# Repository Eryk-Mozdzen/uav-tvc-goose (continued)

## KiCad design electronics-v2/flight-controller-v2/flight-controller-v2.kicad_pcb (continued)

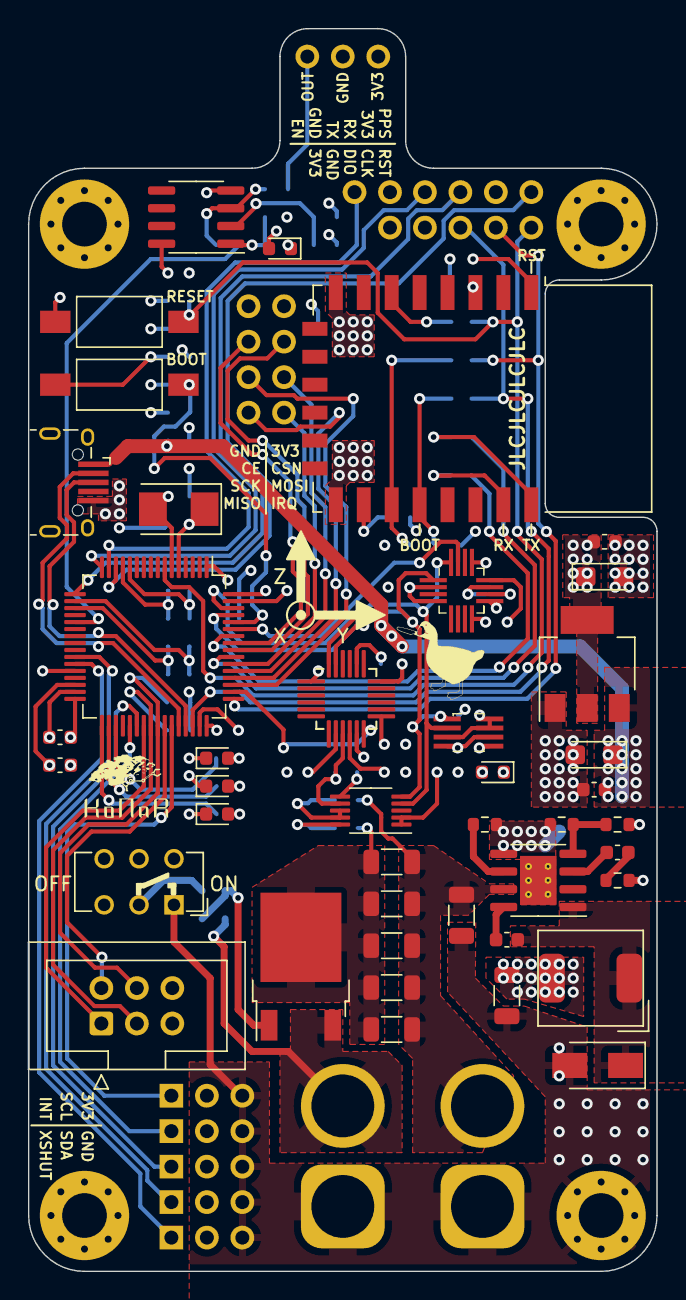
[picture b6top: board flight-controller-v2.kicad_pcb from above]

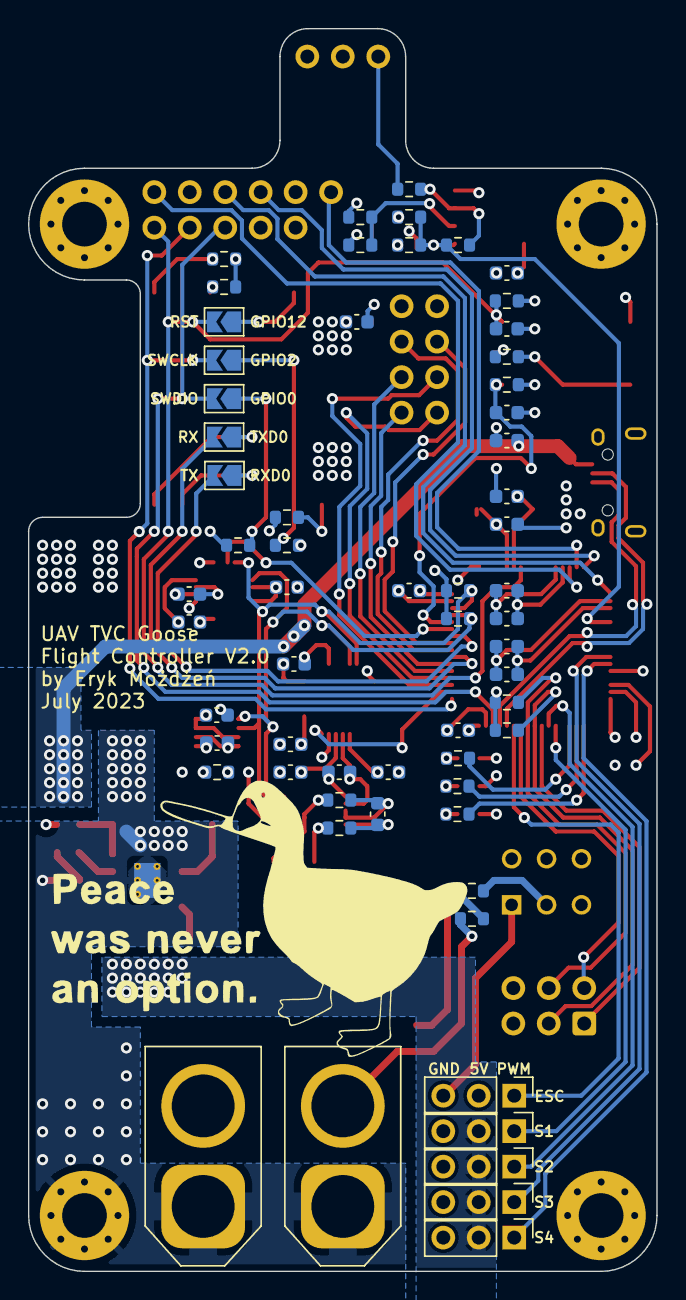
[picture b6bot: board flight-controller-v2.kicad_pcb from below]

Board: 4 copper layers, 45.0 x 89.0 mm, 112 parts (62 on the bottom side), 76 nets.

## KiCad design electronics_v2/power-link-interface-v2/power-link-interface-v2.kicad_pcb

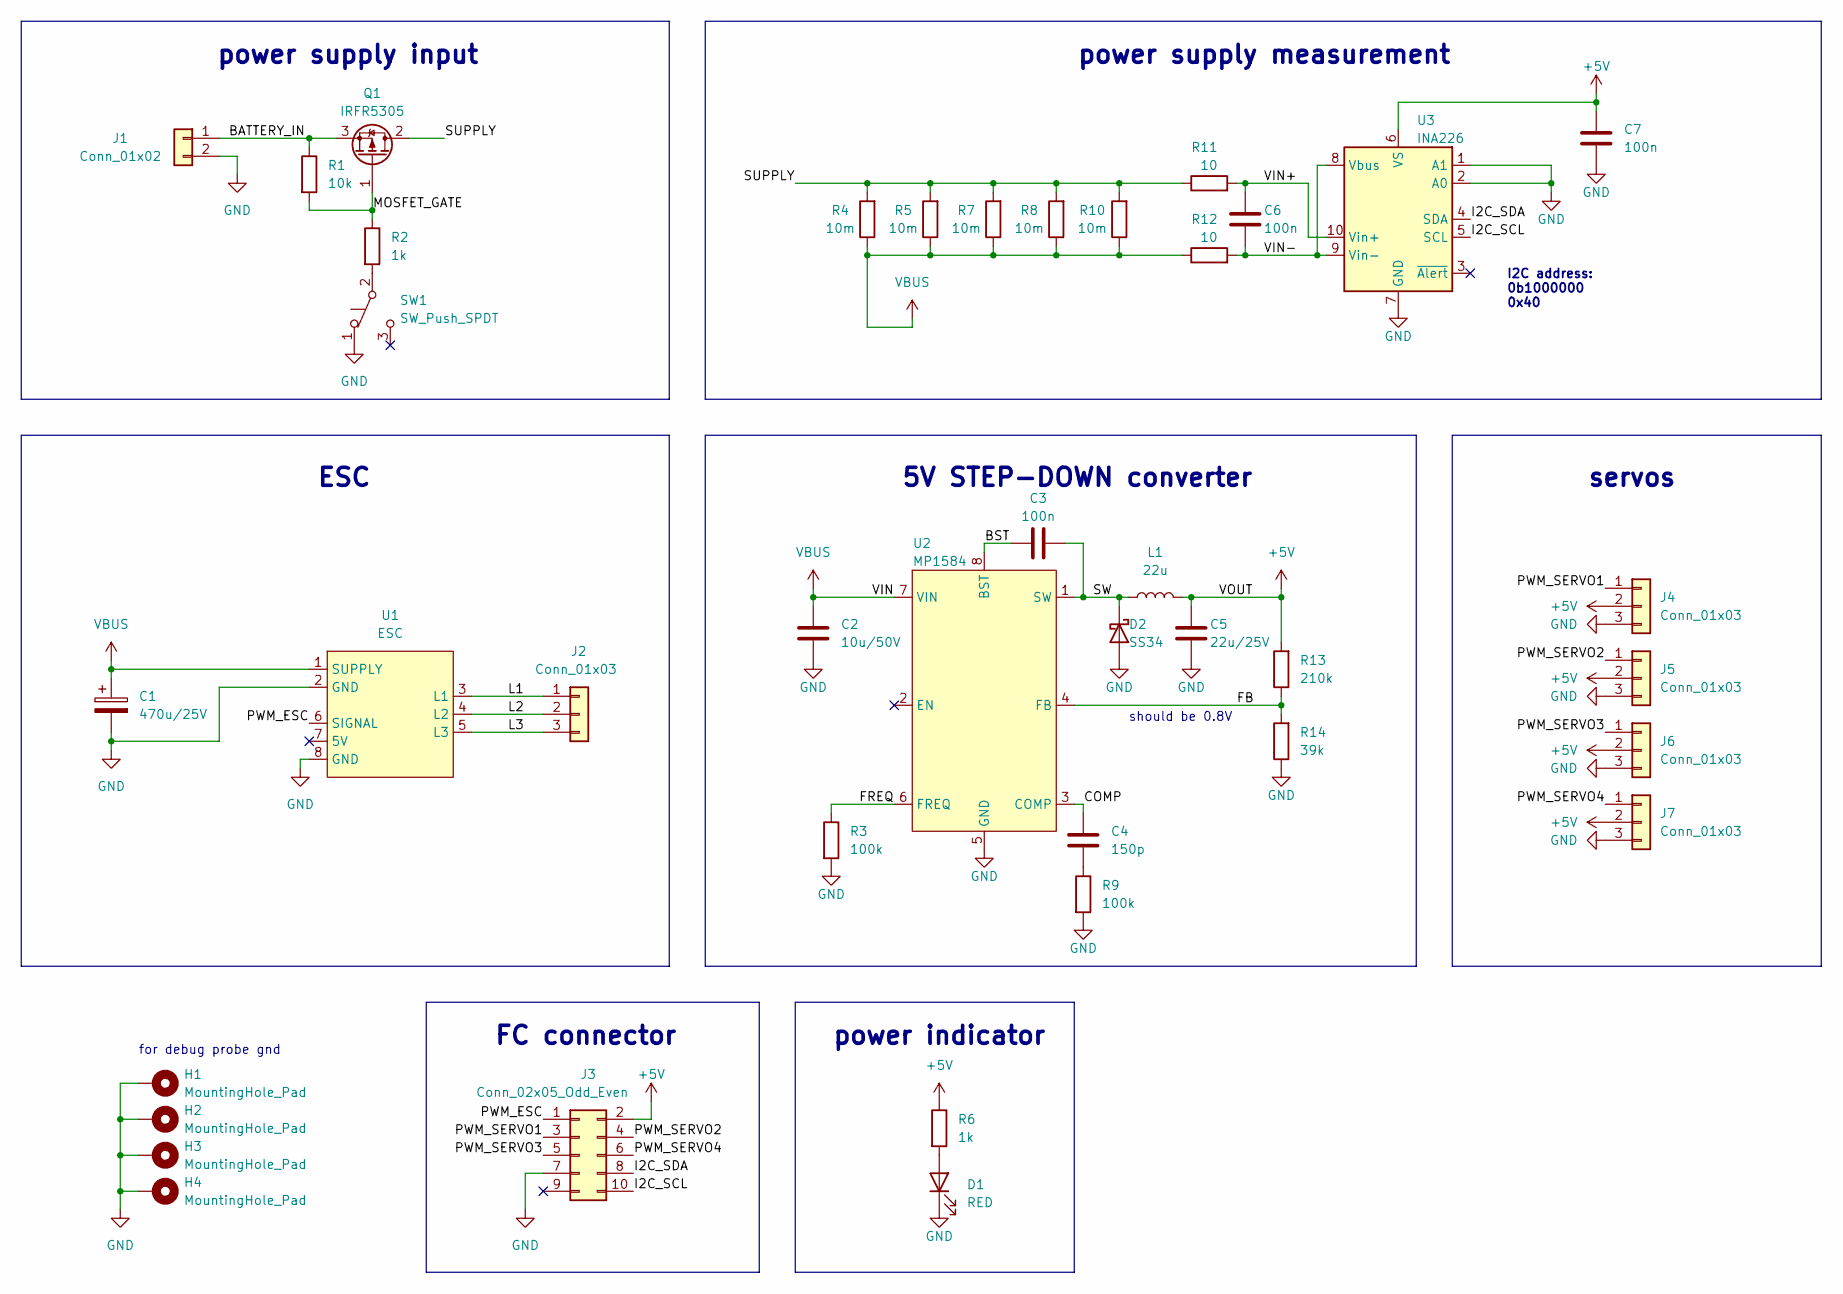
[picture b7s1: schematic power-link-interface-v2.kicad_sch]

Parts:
C1: 470u/25V; C_Radial_D8.0mm_H11.5mm_P3.50mm
C2: 10u/50V; C_1206_3216Metric
C3, C6, C7: 100n; C_0603_1608Metric
C4: 150p; C_0603_1608Metric
C5: 22u/25V; C_1206_3216Metric
D1: RED; LED_0603_1608Metric
D2: SS34; D_SMA
H1, H2, H3, H4: MountingHole_Pad; MountingHole_3.2mm_M3_Pad_Via
J1: Conn_01x02; AMASS_XT60PW-M
J2: Conn_01x03; tht_pin_01x03
J3: Conn_02x05_Odd_Even; IDC-Header_2x05_P2.54mm_Vertical
J4, J5, J6, J7: Conn_01x03; PinHeader_1x03_P2.54mm_Vertical
L1: 22u; L_AVX_LMLP07A7
Q1: IRFR5305; TO-252-2
R1: 10k; R_0603_1608Metric
R2, R6: 1k; R_0603_1608Metric
R3, R9: 100k; R_0603_1608Metric
R4, R5, R7, R8, R10: 10m; R_1206_3216Metric
R11, R12: 10; R_0603_1608Metric
R13: 210k; R_0603_1608Metric
R14: 39k; R_0603_1608Metric
SW1: SW_Push_SPDT; SW_CuK_JS202011CQN_DPDT_Straight
U1: ESC
U2: MP1584; SOIC-8-1EP_3.9x4.9mm_P1.27mm_EP2.62x3.51mm_ThermalVias
U3: INA226; VSSOP-10_3x3mm_P0.5mm

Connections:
+5V: C5.2, C7.2, J3.2, J4.2, J5.2, J6.2, J7.2, L1.2, R6.1, R13.2, U3.6 (VS)
/BATTERY_IN: J1.1, Q1.3 (S), R1.1
/BST: C3.1, U2.8 (BST)
/COMP: C4.1, U2.3 (COMP)
/FB: R13.1, R14.2, U2.4 (FB)
/FREQ: R3.1, U2.6 (FREQ)
/I2C_SCL: J3.10, U3.5 (SCL)
/I2C_SDA: J3.8, U3.4 (SDA)
/L1: J2.1, U1.3 (L1)
/L2: J2.2, U1.4 (L2)
/L3: J2.3, U1.5 (L3)
/MOSFET_GATE: Q1.1 (G), R1.2, R2.1
/PWM_ESC: J3.1, U1.6 (SIGNAL)
/PWM_SERVO1: J3.3, J4.1
/PWM_SERVO2: J3.4, J5.1
/PWM_SERVO3: J3.5, J6.1
/PWM_SERVO4: J3.6, J7.1
/SUPPLY: Q1.2 (D), R4.2, R5.2, R7.2, R8.2, R10.2, R11.1
/SW: C3.2, D2.1 (K), L1.1, U2.1 (SW)
/VIN+: C6.2, R11.2, U3.10 (Vin+)
/VIN-: C6.1, R12.2, U3.8 (Vbus), U3.9 (Vin-)
GND: C1.2, C2.1, C5.1, C7.1, D1.1 (K), D2.2 (A), H1.1, H2.1, H3.1, H4.1, J1.2, J3.7, J4.3, J5.3, J6.3, J7.3, R3.2, R9.2, R14.1, SW1.1 (A), U1.2 (GND), U1.8 (GND), U2.5 (GND), U3.1 (A1), U3.2 (A0), U3.7 (GND)
unnamed: C4.2, R9.1
unnamed: D1.2 (A), R6.2
unnamed: R2.2, SW1.2 (B)
VBUS: C1.1, C2.2, R4.1, R5.1, R7.1, R8.1, R10.1, R12.1, U1.1 (SUPPLY), U2.7 (VIN)

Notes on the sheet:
I2C address: 0b1000000 0x40
FC connector
power supply input
power supply measurement
ESC
for debug probe gnd
power indicator
5V STEP-DOWN converter
servos
should be 0.8V

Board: 2 copper layers, 40 parts (0 on the bottom side), 26 nets, no tracks yet.

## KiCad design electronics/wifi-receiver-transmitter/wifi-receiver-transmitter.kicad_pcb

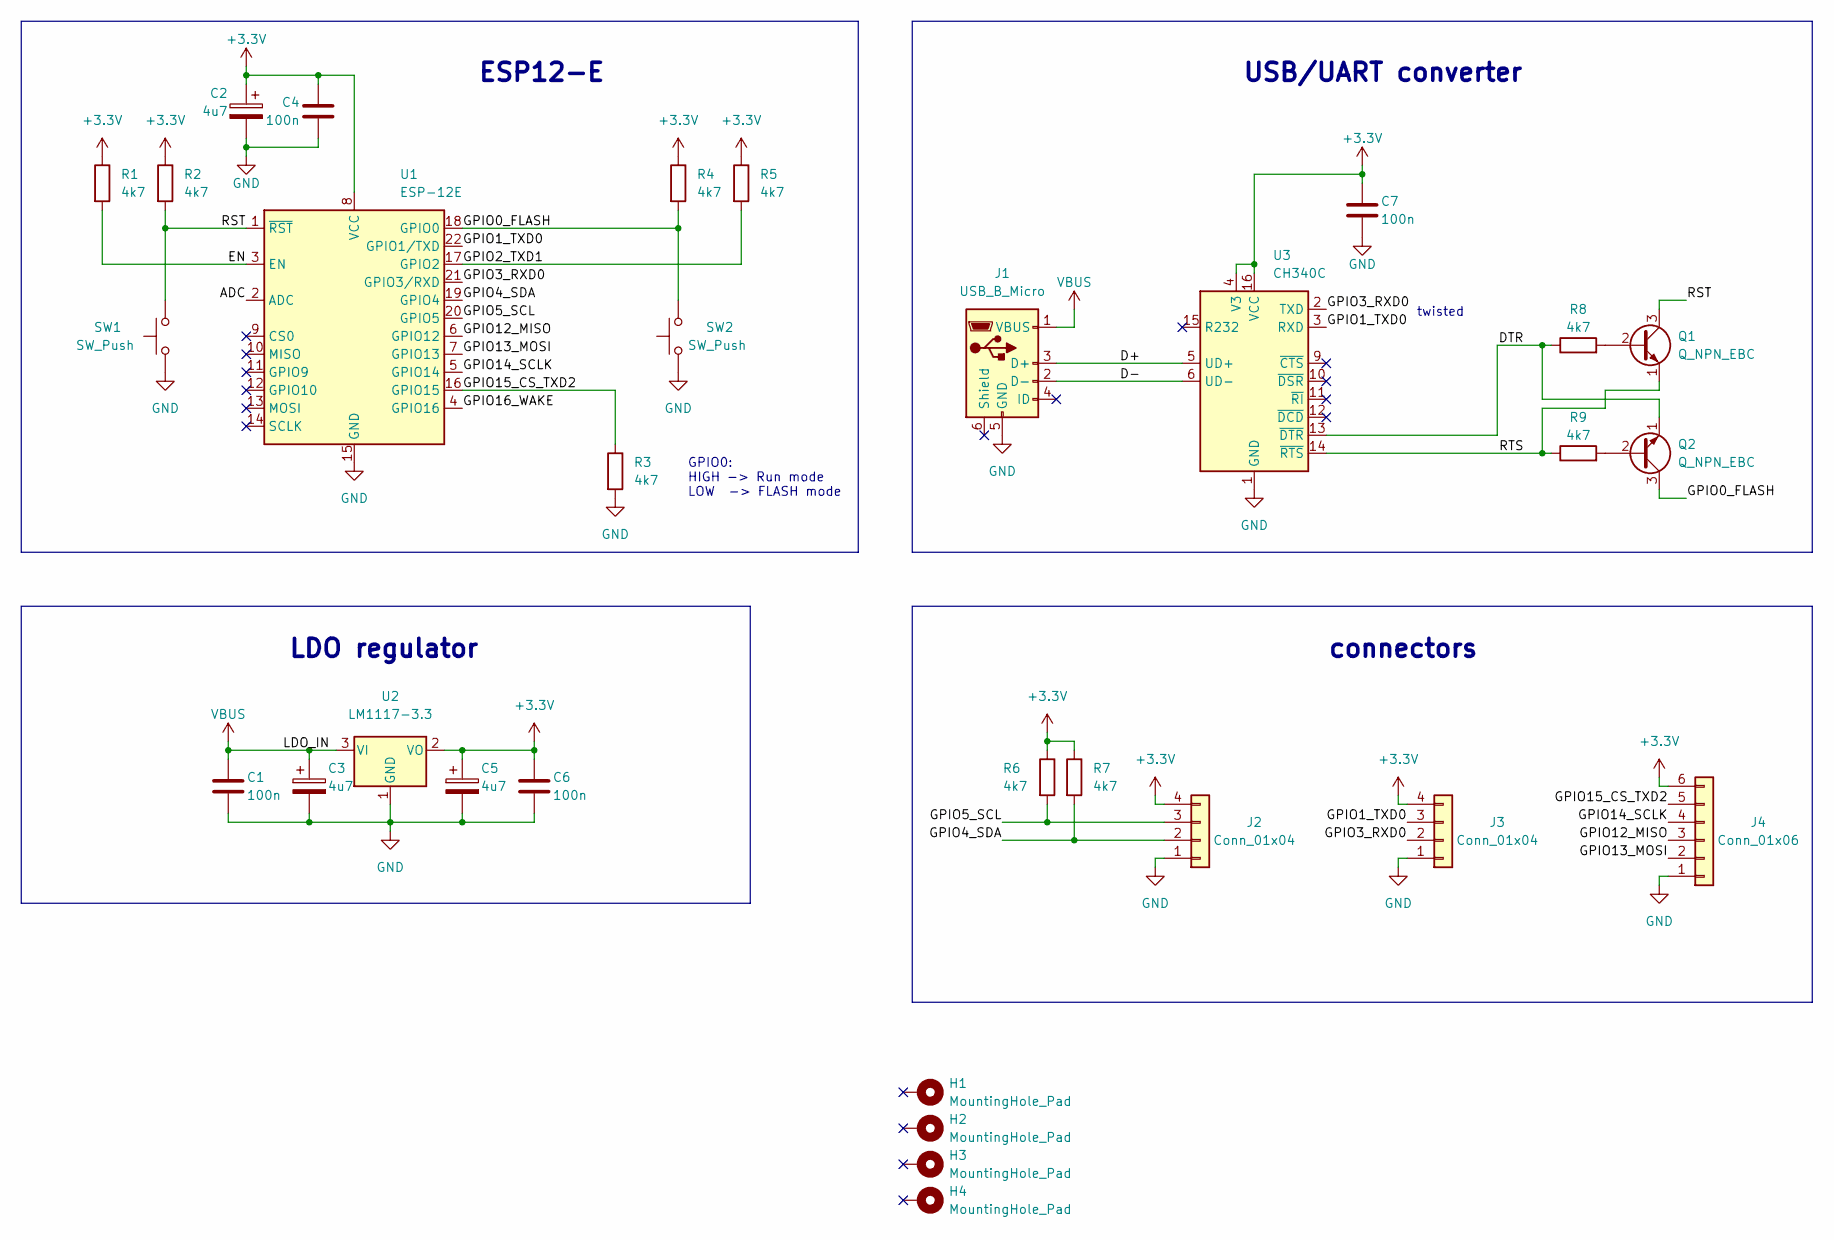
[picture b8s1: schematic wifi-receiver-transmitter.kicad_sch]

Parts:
C1, C4, C6, C7: 100n; C_0603_1608Metric
C2, C3, C5: 4u7; CP_EIA-3216-18_Kemet-A
H1, H2, H3, H4: MountingHole_Pad; MountingHole_3.2mm_M3_Pad_Via
J1: USB_B_Micro; usb_micro_B_druk_II
J2, J3: Conn_01x04; tht_pin_01x04
J4: Conn_01x06; tht_pin_01x06
Q1, Q2: Q_NPN_EBC; SOT-23
R1, R2, R3, R4, R5, R6, R7, R8, R9: 4k7; R_0603_1608Metric
SW1, SW2: SW_Push; SW_Push_SPST_NO_Alps_SKRK
U1: ESP-12E
U2: LM1117-3.3; SOT-223-3_TabPin2
U3: CH340C; SOIC-16_3.9x9.9mm_P1.27mm

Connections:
+3.3V: C2.1, C4.1, C5.1, C6.1, C7.1, J2.4, J3.4, J4.6, R1.1, R2.1, R4.1, R5.1, R6.1, R7.1, U1.8 (VCC), U2.2 (VO), U3.4 (V3), U3.16 (VCC)
/ADC: U1.2 (ADC)
/D+: J1.3 (D+), U3.5 (UD+)
/D-: J1.2 (D-), U3.6 (UD-)
/DTR: Q2.1 (E), R8.1, U3.13 (~DTR)
/EN: R1.2, U1.3 (EN)
/GPIO0_FLASH: Q2.3 (C), R4.2, SW2.2, U1.18 (GPIO0)
/GPIO1_TXD0: J3.3, U1.22 (GPIO1/TXD), U3.3 (RXD)
/GPIO2_TXD1: R5.2, U1.17 (GPIO2)
/GPIO3_RXD0: J3.2, U1.21 (GPIO3/RXD), U3.2 (TXD)
/GPIO4_SDA: J2.2, R7.2, U1.19 (GPIO4)
/GPIO5_SCL: J2.3, R6.2, U1.20 (GPIO5)
/GPIO12_MISO: J4.3, U1.6 (GPIO12)
/GPIO13_MOSI: J4.2, U1.7 (GPIO13)
/GPIO14_SCLK: J4.4, U1.5 (GPIO14)
/GPIO15_CS_TXD2: J4.5, R3.1, U1.16 (GPIO15)
/GPIO16_WAKE: U1.4 (GPIO16)
/RST: Q1.3 (C), R2.2, SW1.2, U1.1 (~RST)
/RTS: Q1.1 (E), R9.1, U3.14 (~RTS)
GND: C1.2, C2.2, C3.2, C4.2, C5.2, C6.2, C7.2, J1.5 (GND), J2.1, J3.1, J4.1, R3.2, SW1.1, SW2.1, U1.15 (GND), U2.1 (GND), U3.1 (GND)
unnamed: Q1.2 (B), R8.2
unnamed: Q2.2 (B), R9.2
VBUS: C1.1, C3.1, J1.1 (VBUS), U2.3 (VI)

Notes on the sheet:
ESP12-E
USB/UART converter
GPIO0: HIGH -> Run mode LOW -> FLASH mode
LDO regulator
twisted
connectors

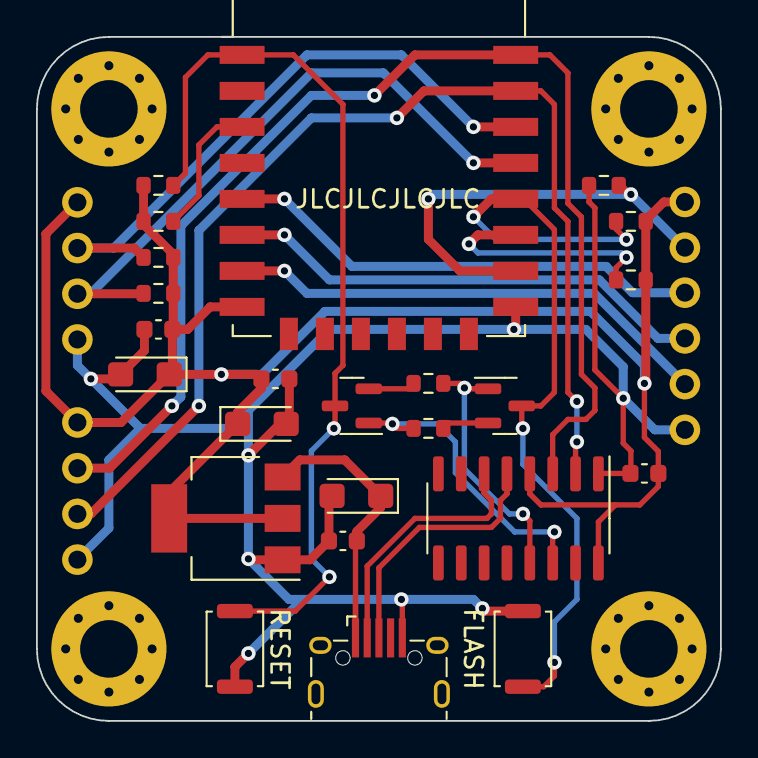
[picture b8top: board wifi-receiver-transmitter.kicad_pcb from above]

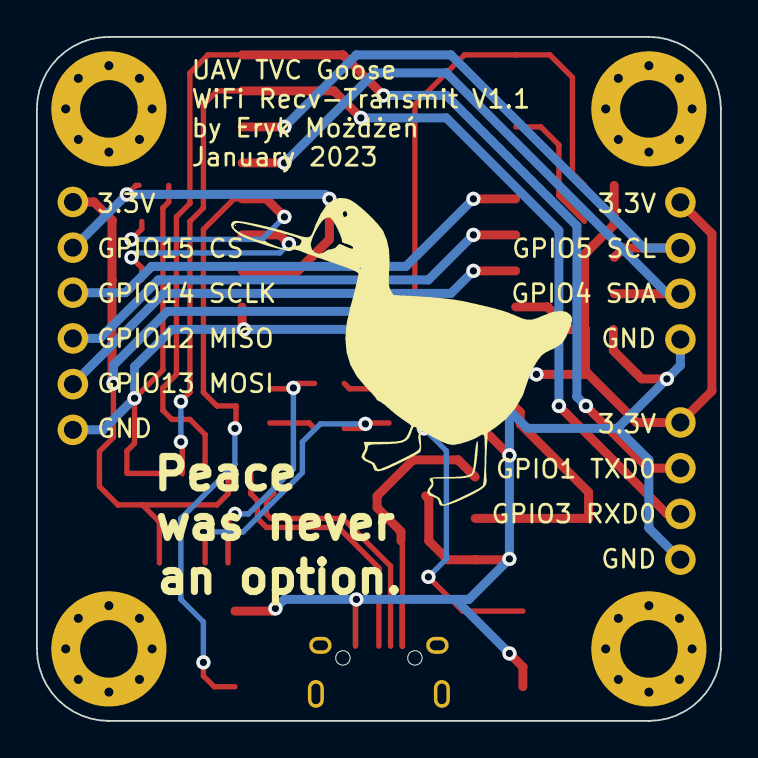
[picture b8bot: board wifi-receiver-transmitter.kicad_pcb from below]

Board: 2 copper layers, 38.0 x 38.0 mm, 31 parts (2 on the bottom side), 21 nets.

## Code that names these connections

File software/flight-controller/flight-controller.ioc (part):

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Mcu.Name=STM32U535RETx
Mcu.Package=LQFP64
Mcu.UserName=STM32U535RETx
PA0.GPIOParameters=GPIO_Label
PA0.GPIO_Label=TACHO
PA0.Signal=S_TIM2_ETR
PA10.GPIOParameters=GPIO_Label
PA10.GPIO_Label=SERVO1
PA10.Signal=S_TIM1_CH3
PA11.GPIOParameters=GPIO_Label
PA11.GPIO_Label=ESC
PA11.Signal=S_TIM1_CH4
PA13\ (JTMS/SWDIO).Mode=Serial_Wire
PA13\ (JTMS/SWDIO).Signal=DEBUG_JTMS-SWDIO
PA14\ (JTCK/SWCLK).Mode=Serial_Wire
PA14\ (JTCK/SWCLK).Signal=DEBUG_JTCK-SWCLK
PA4.GPIOParameters=GPIO_Label
PA4.GPIO_Label=FLOW_CS
PA4.Signal=GPIO_Output
PA5.GPIOParameters=GPIO_Label
PA5.GPIO_Label=FLOW_SCK
PA5.Mode=Full_Duplex_Master
PA5.Signal=SPI1_SCK
PA6.GPIOParameters=GPIO_Label
PA6.GPIO_Label=FLOW_MISO
PA6.Mode=Full_Duplex_Master
PA6.Signal=SPI1_MISO
PA7.GPIOParameters=GPIO_Label
PA7.GPIO_Label=FLOW_MOSI
PA7.Mode=Full_Duplex_Master
PA7.Signal=SPI1_MOSI
PA8.GPIOParameters=GPIO_Label
PA8.GPIO_Label=SERVO3
PA8.Signal=S_TIM1_CH1
PA9.GPIOParameters=GPIO_Label
PA9.GPIO_Label=SERVO2
PA9.Signal=S_TIM1_CH2
PB1.GPIOParameters=GPIO_Label
PB1.GPIO_Label=LED_G
PB1.Signal=GPIO_Output
PB12.GPIOParameters=GPIO_Label
PB12.GPIO_Label=LED_R
PB12.Signal=GPIO_Output
PB15.GPIOParameters=GPIO_Label,GPIO_ModeDefaultEXTI
PB15.GPIO_Label=RANGE_ECHO
PB15.GPIO_ModeDefaultEXTI=GPIO_MODE_IT_RISING_FALLING
PB15.Signal=GPXTI15
PB2.GPIOParameters=GPIO_Label
PB2.GPIO_Label=LED_B
PB2.Signal=GPIO_Output
PB3\ (JTDO/TRACESWO).GPIOParameters=GPIO_Label
PB3\ (JTDO/TRACESWO).GPIO_Label=IMU_INT
PB3\ (JTDO/TRACESWO).Signal=GPXTI3
PB5.GPIOParameters=GPIO_Label,GPIO_ModeDefaultEXTI
PB5.GPIO_Label=PWR_INT
PB5.GPIO_ModeDefaultEXTI=GPIO_MODE_IT_FALLING
PB5.Signal=GPXTI5
PB6.GPIOParameters=GPIO_Speed,GPIO_Label
PB6.GPIO_Label=MISC_SCL
PB6.GPIO_Speed=GPIO_SPEED_FREQ_VERY_HIGH
PB6.Mode=I2C
PB6.Signal=I2C4_SCL
PB7.GPIOParameters=GPIO_Speed,GPIO_Label
PB7.GPIO_Label=MISC_SDA
PB7.GPIO_Speed=GPIO_SPEED_FREQ_VERY_HIGH
PB7.Mode=I2C
PB7.Signal=I2C4_SDA
PB8.GPIOParameters=GPIO_Speed,GPIO_Label
PB8.GPIO_Label=IMU_SCL
PB8.GPIO_Speed=GPIO_SPEED_FREQ_VERY_HIGH
PB8.Mode=I2C
PB8.Signal=I2C1_SCL
PB9.GPIOParameters=GPIO_Speed,GPIO_Label
PB9.GPIO_Label=IMU_SDA
PB9.GPIO_Speed=GPIO_SPEED_FREQ_VERY_HIGH
PB9.Mode=I2C
PB9.Signal=I2C1_SDA
PC0.GPIOParameters=GPIO_Speed,GPIO_Label
PC0.GPIO_Label=MAG_SCL
PC0.GPIO_Speed=GPIO_SPEED_FREQ_VERY_HIGH
PC0.Mode=I2C
PC0.Signal=I2C3_SCL
PC1.GPIOParameters=GPIO_Speed,GPIO_Label
PC1.GPIO_Label=MAG_SDA
PC1.GPIO_Speed=GPIO_SPEED_FREQ_VERY_HIGH
PC1.Mode=I2C
PC1.Signal=I2C3_SDA
PC10.GPIOParameters=GPIO_Label
PC10.GPIO_Label=ESP_RXD
PC10.Mode=Asynchronous
PC10.Signal=UART4_TX
PC11.GPIOParameters=GPIO_Label
PC11.GPIO_Label=ESP_TXD
PC11.Mode=Asynchronous
PC11.Signal=UART4_RX
PC12.GPIOParameters=GPIO_Label
PC12.GPIO_Label=GPS_RXD
PC12.Mode=Asynchronous
PC12.Signal=UART5_TX
PC13.GPIOParameters=GPIO_Label
PC13.GPIO_Label=LOAD_RATE
PC13.Signal=GPIO_Output
PC14-OSC32_IN\ (PC14).GPIOParameters=GPIO_Label
PC14-OSC32_IN\ (PC14).GPIO_Label=LOAD_DOUT
PC14-OSC32_IN\ (PC14).Signal=GPIO_Input
PC15-OSC32_OUT\ (PC15).GPIOParameters=GPIO_Label
PC15-OSC32_OUT\ (PC15).GPIO_Label=LOAD_SCK
PC15-OSC32_OUT\ (PC15).Signal=GPIO_Output
PC2.GPIOParameters=GPIO_Label
PC2.GPIO_Label=MAG_INT
PC2.Signal=GPXTI2
PC4.GPIOParameters=GPIO_Label,GPIO_ModeDefaultEXTI
PC4.GPIO_Label=FLOW_INT
PC4.GPIO_ModeDefaultEXTI=GPIO_MODE_IT_FALLING
PC4.Signal=GPXTI4
PC6.GPIOParameters=GPIO_Label
PC6.GPIO_Label=RANGE_TRIG
PC6.Signal=S_TIM8_CH1
PD2.GPIOParameters=GPIO_Label
PD2.GPIO_Label=GPS_TXD
PD2.Mode=Asynchronous
PD2.Signal=UART5_RX
PH0-OSC_IN\ (PH0).Mode=HSE-External-Oscillator
PH0-OSC_IN\ (PH0).Signal=RCC_OSC_IN
PH1-OSC_OUT\ (PH1).Mode=HSE-External-Oscillator
PH1-OSC_OUT\ (PH1).Signal=RCC_OSC_OUT
RCC.HSE_VALUE=8000000
RCC.SYSCLKFreq_VALUE=160000000
RCC.SYSCLKSource=RCC_SYSCLKSOURCE_PLLCLK
board=custom

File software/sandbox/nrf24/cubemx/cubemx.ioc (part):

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Mcu.Name=STM32U083RCTx
Mcu.Package=LQFP64
Mcu.UserName=STM32U083RCTx
PA1.Mode=Full_Duplex_Master
PA1.Signal=SPI2_SCK
PA10.Signal=GPIO_Output
PA2.Mode=Asynchronous
PA2.Signal=USART2_TX
PA3.Mode=Asynchronous
PA3.Signal=USART2_RX
PA5.Signal=GPIO_Output
PA8.Signal=GPIO_Output
PB3.Mode=Full_Duplex_Master
PB3.Signal=SPI1_SCK
PB4.Mode=Full_Duplex_Master
PB4.Signal=SPI1_MISO
PB5.Mode=Full_Duplex_Master
PB5.Signal=SPI1_MOSI
PC0.Signal=GPIO_Output
PC1.Signal=GPIO_Output
PC13.GPIOParameters=GPIO_PuPd
PC13.GPIO_PuPd=GPIO_PULLUP
PC13.Signal=GPIO_Input
PC2.Mode=Full_Duplex_Master
PC2.Signal=SPI2_MISO
PC3.Mode=Full_Duplex_Master
PC3.Signal=SPI2_MOSI
RCC.HSE_VALUE=4000000
RCC.SYSCLKFreq_VALUE=56000000
RCC.SYSCLKSource=RCC_SYSCLKSOURCE_PLLCLK
board=custom

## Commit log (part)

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2023-04-16 better icons and colors
2023-04-16 battery and fill
2023-04-16 better scaling
2023-04-16 smooth colors
2023-04-16 add voltage and current
2023-04-16 add altimeter
2023-04-17 add constrain to level
2023-04-17 add prefix to battery level
2023-04-17 remove battery prefix
2023-04-18 moved units
2023-04-18 removed empty line
2023-04-18 add USB data queue
2023-04-18 reverse order of byts in usb work xd
2023-04-25 add first comments
2023-05-04 signle mesurement work
2023-05-05 VLX work on interrupt
2023-05-05 moce read to task
2023-05-05 add slave recovery, increase queues
2023-05-09 Added scene without measurements
2023-05-09 logger show real data
2023-05-09 add doxygen comments
2023-05-09 simpler cmake, recursion
2023-05-20 power stats task
2023-05-20 ADC over DMA and scaling
2023-05-20 move sensor telemetry from estimator to sensors
2023-05-20 add const interval also to power and pressure
2023-05-21 move attitude estimation to separate class
2023-05-21 start of altitude and battery estimators
2023-05-21 increase timer queue length
2023-05-21 add high water mark for stack and decrease stacks
2023-05-22 dist compensation, simple kalman
2023-05-22 battery display real data
2023-05-22 altimeter show real data
2023-05-22 add ??? at data timeout
2023-05-23 added RPY
2023-05-23 state and command
2023-05-23 Vector class in now constexpr
2023-05-23 batter calibration values
2023-05-24 automatic source switch between barometer and TOF
2023-05-24 increase observation covariance of barometer, add switch messages
2023-05-25 add AFFRLS
2023-05-25 converter discret to physical
2023-05-26 completed view with ???
2023-05-26 removed mtl file
2023-05-26 use only EKF, generate best fit polynomial
2023-05-27 added actuators read usb
2023-05-27 docs updated
2023-05-28 add state machine diagram
2023-05-28 fixed square 3dscene
2023-05-28 changed axis
2023-05-28 no more matrix
2023-05-30 fix frames
2023-06-01 add state machine as submodule and define states
2023-06-01 add simple events
2023-06-03 add gamepad controller input to setpoint
2023-06-03 add logs, fix serial
2023-06-03 add power stats
2023-06-04 estimator and controller data frames, queue for state
2023-06-04 add combination event
2023-06-04 add movement event
2023-06-04 add altitude reacher event
2023-06-04 resetting events in takeoff/landing states
2023-06-06 update physical values
2023-06-06 LQR controller
2023-06-06 automatic landing
2023-06-06 automatic take off
2023-06-06 add wireless data to app
2023-06-06 correct PWM for ESC
2023-06-07 state amchine code cleaning
2023-06-14 add separate models for system and measurements
2023-06-17 update pressure derivative
2023-06-17 update station app
2023-06-17 send ground pressure estimation
2023-06-17 remove debug acc printing
2023-06-20 Google Maps markers
2023-06-21 switch to OpenStreetMap
2023-06-21 move map to separate widget class
2023-06-22 cleaning
2023-06-28 perform prop test
2023-06-28 move code to sandbox
2023-06-29 add weight measurements
2023-07-01 update weights
2023-07-08 add memory preview
2023-07-08 station app refactor
2023-07-08 add RAM copy to easy access
2023-07-09 add simulation from RM1 repo
2023-07-12 develop Hall velocity sense circuit
2023-07-12 FC scheme complete
2023-07-12 first board cutout and layout
2023-07-13 add 3d models to custom footprints
2023-07-13 start of Power Link Interface
2023-07-18 PLI work
2023-07-18 edge XT60 connector & INA226 I2C measurement
2023-07-18 move XT60 to center of the edge
2023-07-19 update docs
2023-07-20 movemounting hole by 0.1mm
2023-07-20 fix route names
2023-07-21 script for thrust params
2023-07-22 data strored in CSV file
2023-07-23 rotor torque coefficent
2023-07-23 calculate also u_0
2023-07-24 fix curve fitting
2023-07-24 add link to 3d model
2023-07-25 add paper about lift coefficient
2023-07-26 add read model to simulation
2023-07-26 add fins movement
2023-07-26 update link
2023-07-27 add hall to program scheme
2023-07-27 route new FC
2023-07-27 change folder name
2023-07-29 fixes in routing
2023-07-30 fix segfault on exit when telnet is used
2023-07-30 create simple external receiver
2023-07-31 add on/off text near switch
2023-07-31 generate schematic
2023-07-31 add auto reconnect gamepad
2023-07-31 remove unnessary code
2023-08-02 update parameters, improve performance, fix model in visualization
2023-08-03 fix route name, remove ADC code
2023-08-03 update ESC PWM channel to new one
2023-08-03 move ESP UART1 RX from PB7 to PB3
2023-08-03 update MAG INT pin from PB5 to PB7
2023-08-03 add code to handle RGB lights
2023-08-03 implmentation of Hall efect sensor based motor velocity reader
2023-08-03 display motor velocity in station app
2023-08-04 add integral to LQR
2023-08-04 add integral term to controller in FC
2023-08-04 start of calib app
2023-08-04 automatic removing 3 sigma samples
2023-08-05 use of best fit ellipsoid to match data WORK
2023-08-05 automatic window scaling, remove xy, xz yz params from fitting, better aoutput formatting
2023-08-05 crate simple app
2023-08-05 change names to new convention
2023-08-05 reset integral before every flight
2023-08-06 remove automatic take off and add abort cmd
2023-08-06 commands generated from gamepad buttons
2023-08-16 move runtime stats to timer 5
2023-08-17 INA226 read fix
2023-08-17 fix IMU axes
2023-08-18 calibration of acc and mag
2023-08-18 fix Vref in Hall comeprator, update schematic, add moving average to vel
2023-08-18 fix velocity calculation
2023-08-19 remove unused VLX I2C interrupts
2023-08-19 add OTA flash option
2023-08-20 tests with 4 fins
2023-08-21 add ramp to throttle
2023-08-21 fix ramp
2023-08-23 fix steering and default ip address
2023-08-24 more stable Q and R
2023-08-27 tests of 8 thrust vanes
2023-08-28 update simulation to octa version
2023-09-07 clean up simulation
2023-09-09 state limits over 0.5s
2023-09-10 remove memory feature
2023-09-10 simple chart
2023-09-11 add dashed line
2023-09-12 pause at abort
2023-09-12 use modern way to create axes
2023-09-12 add RESET command
2023-09-13 change ranges in charts
2023-09-17 add axes labels and chart title
2023-09-21 update state machine
2023-09-23 add vel chart, switch to vel control in Z
2023-09-23 remove yaw from station
2023-09-26 more tests
2023-09-26 fix strange merge
2023-09-26 remove VLX, add simple code for ultrasonic
2023-09-27 add check for out-of-range
2023-10-08 better K
2023-10-20 better manual control
2023-10-21 FIRST TIME WORK
2023-10-22 full best fit ellipsoid (offset, scale, rotation), use of Eigen
2023-10-22 make viewer normal object not pointer
2023-10-22 use std::vector
2023-10-22 smaller points
2023-10-22 remove eigen include dir
2023-10-29 simple app
2023-10-30 add type to manual control
2023-10-30 3 value calibration
2023-10-31 docs actualization
2023-11-01 remove deg logs from events
2023-11-01 vertical velocity chart, remove old saples
2023-11-01 fix matrix writing to header file
2023-11-03 add old reports from university
2023-11-10 fix yaw telemetry sending
2023-11-13 fix label in acc calib
2023-11-14 least sqares method for accelerometer calibration
2023-11-14 simpler acceleromwter calibration calculations
2023-11-15 remove cross coupling
2023-11-15 add multiple samples per predefine orientation
2023-11-16 update model parameters
2023-11-19 improve Telnet transmitter
2023-12-14 add test histeresis screen
2023-12-15 fixes
2023-12-16 correct thrust measurements NEED TEST
2023-12-17 diffrent interpretation of identyfication results
2024-06-01 schematic start
2024-06-02 sensors, power, actuators, filters
2024-06-22 Simple3
2024-06-22 offline calculation
2024-06-26 tests
2024-07-13 experiments settings
2024-07-13 automatic thrust test
2024-07-14 load cell calibration
2024-07-14 fix start throttle and thrust script, 100 samples
2024-07-14 schematic cleanup
2024-07-26 still working
2024-07-26 simplify protocol
2024-07-27 clean footprints
2024-07-27 PI LC filters values
2024-07-28 clean models
2024-07-28 switches footprints
2024-07-28 fix footprint
2024-07-28 aux schamtics
2024-07-29 aux clean footprints
2024-07-29 aux test layout
2024-07-29 ready?
2024-07-31 Mouser
2024-08-01 routing: first blood
2024-08-02 routing: rought placement
2024-08-03 tested
2024-08-04 routing: silkscreen
2024-08-05 fix IMU interrupt
2024-08-05 fix connector GPS pinout, update AUX pinouts
2024-08-06 routing: AUX all
2024-08-06 3D models
2024-08-06 gerbers
2024-08-06 routing: AUX panel fix
2024-08-07 panel V3
2024-08-08 new gerbers
2024-08-08 generate schematic in pdf
2024-08-08 generate new 3D models
2024-08-10 CRC at the end
2024-08-10 serial widget
2024-08-10 network interface, automatic IP scan, fix protocol bug
2024-08-11 better Network widget
2024-08-11 centering
2024-08-11 network connection not break terminal
2024-08-11 abstract interface for network & serial
2024-08-11 apply new interfaces to calibration app
2024-08-11 remove additional inner layout
2024-08-13 add serial from 2nd repo
2024-08-15 QCustomPlot with OpenGL, Protocol wrapper separate thread
2024-08-15 Meshcat visualizer + self made gamepad
2024-08-15 use my custom visualizer in separate process + respown button
2024-08-16 inform user about gamepad error
2024-08-16 add time in msg frame, use uC time as timebase for live plots
2024-08-16 remove all unseen sampless from plot
2024-08-16 add light mode checkbox for 3d server
2024-08-17 connect all signals to plots/forms
2024-08-17 visualization in separate thread
2024-08-17 use 230400 baudrate for serial
2024-08-19 update identification app
2024-08-19 add velocity, current and voltage to csv file
2024-08-19 calculate rotor velocity w(u) and F(w) and M(w)
2024-08-22 add controller script
2024-08-26 start
2024-08-27 communication, IMU, MAG work
2024-08-28 GPS work
2024-08-28 RANGE work
2024-08-28 FLOW work (blocking)
2024-08-28 TACHO work
2024-08-30 core load estimation, LOAD is not a problem, FLOW work (non-blocking)
2024-08-30 add old estimator.py script, optimalize CMSIS-DSP, run EKF on 1kHz data from IMU
2024-08-31 first promising use of FLOW in sensor fusion
2024-09-01 FLOW and ACCEL work better
2024-09-01 state machine, -K(x-xd)+u0 controller, state limits
2024-09-04 TACH on optical sensor CNY70, UART software watchdog
2024-09-05 fix identyfication app and script
2024-09-06 perform motor identification with TACHO
2024-09-06 fix NVM, but still is not relaiable
2024-09-08 fix NVM
2024-09-09 use correct coord. frame for FLOW
2024-09-09 model params, fix servo direction, protection against spikes from FLOW, pause plots on abort, auto resume on start
2024-09-12 marge plots together
2024-09-14 fix controller signs, ESC off on throttle 0%
2024-09-16 add psi to K matrix
2024-09-17 add integral action
2024-11-24 prediction/control horizon, 6 dim trajectory, 100Hz
2024-11-24 MPC dev
2024-11-25 better model
2024-11-27 MPC work as trajectory converter
2024-12-02 sympy Goose II model with feedback linearization (not work yet)
2024-12-02 feedback linearization MIMO WORK (but only for phi thet psi without z)
2024-12-03 feedback lineariztion work on phi theta psi thrust
2024-12-03 MPC work with new feedback linearization
2024-12-06 MPC add constraints to state
2024-12-06 state constraints only for thrust force
2024-12-06 add phi/theta to cost function
2024-12-07 better labels
2024-12-10 code generation work
2024-12-10 drake + MPC integration, oscillations
2024-12-10 fix motor model
2024-12-18 drake + open + sympy MPC work
2024-12-21 MPC from sympy linearized model WORK WELL
2024-12-21 plot reference trajectory
2024-12-21 3D visualization server from CSV
2024-12-22 opimize pos, vel, accel in MPC trajectory
2025-12-07 STM32U0 C++ RTOS project
2025-12-09 firmware architecture concept
2025-12-10 stilled code for nRF24 from internet
2025-12-10 remove trash
2025-12-13 rx tx objects
2025-12-13 add config for 2nd nrf
2025-12-14 lightweight custom foramtter
2025-12-14 ostream initial
2025-12-14 fix float printing
2025-12-15 fix assert
2025-12-17 wip: add reference to spi handle
2025-12-17 wip: nrf wip
2025-12-20 wip: first stable communication via nRF24L01+
